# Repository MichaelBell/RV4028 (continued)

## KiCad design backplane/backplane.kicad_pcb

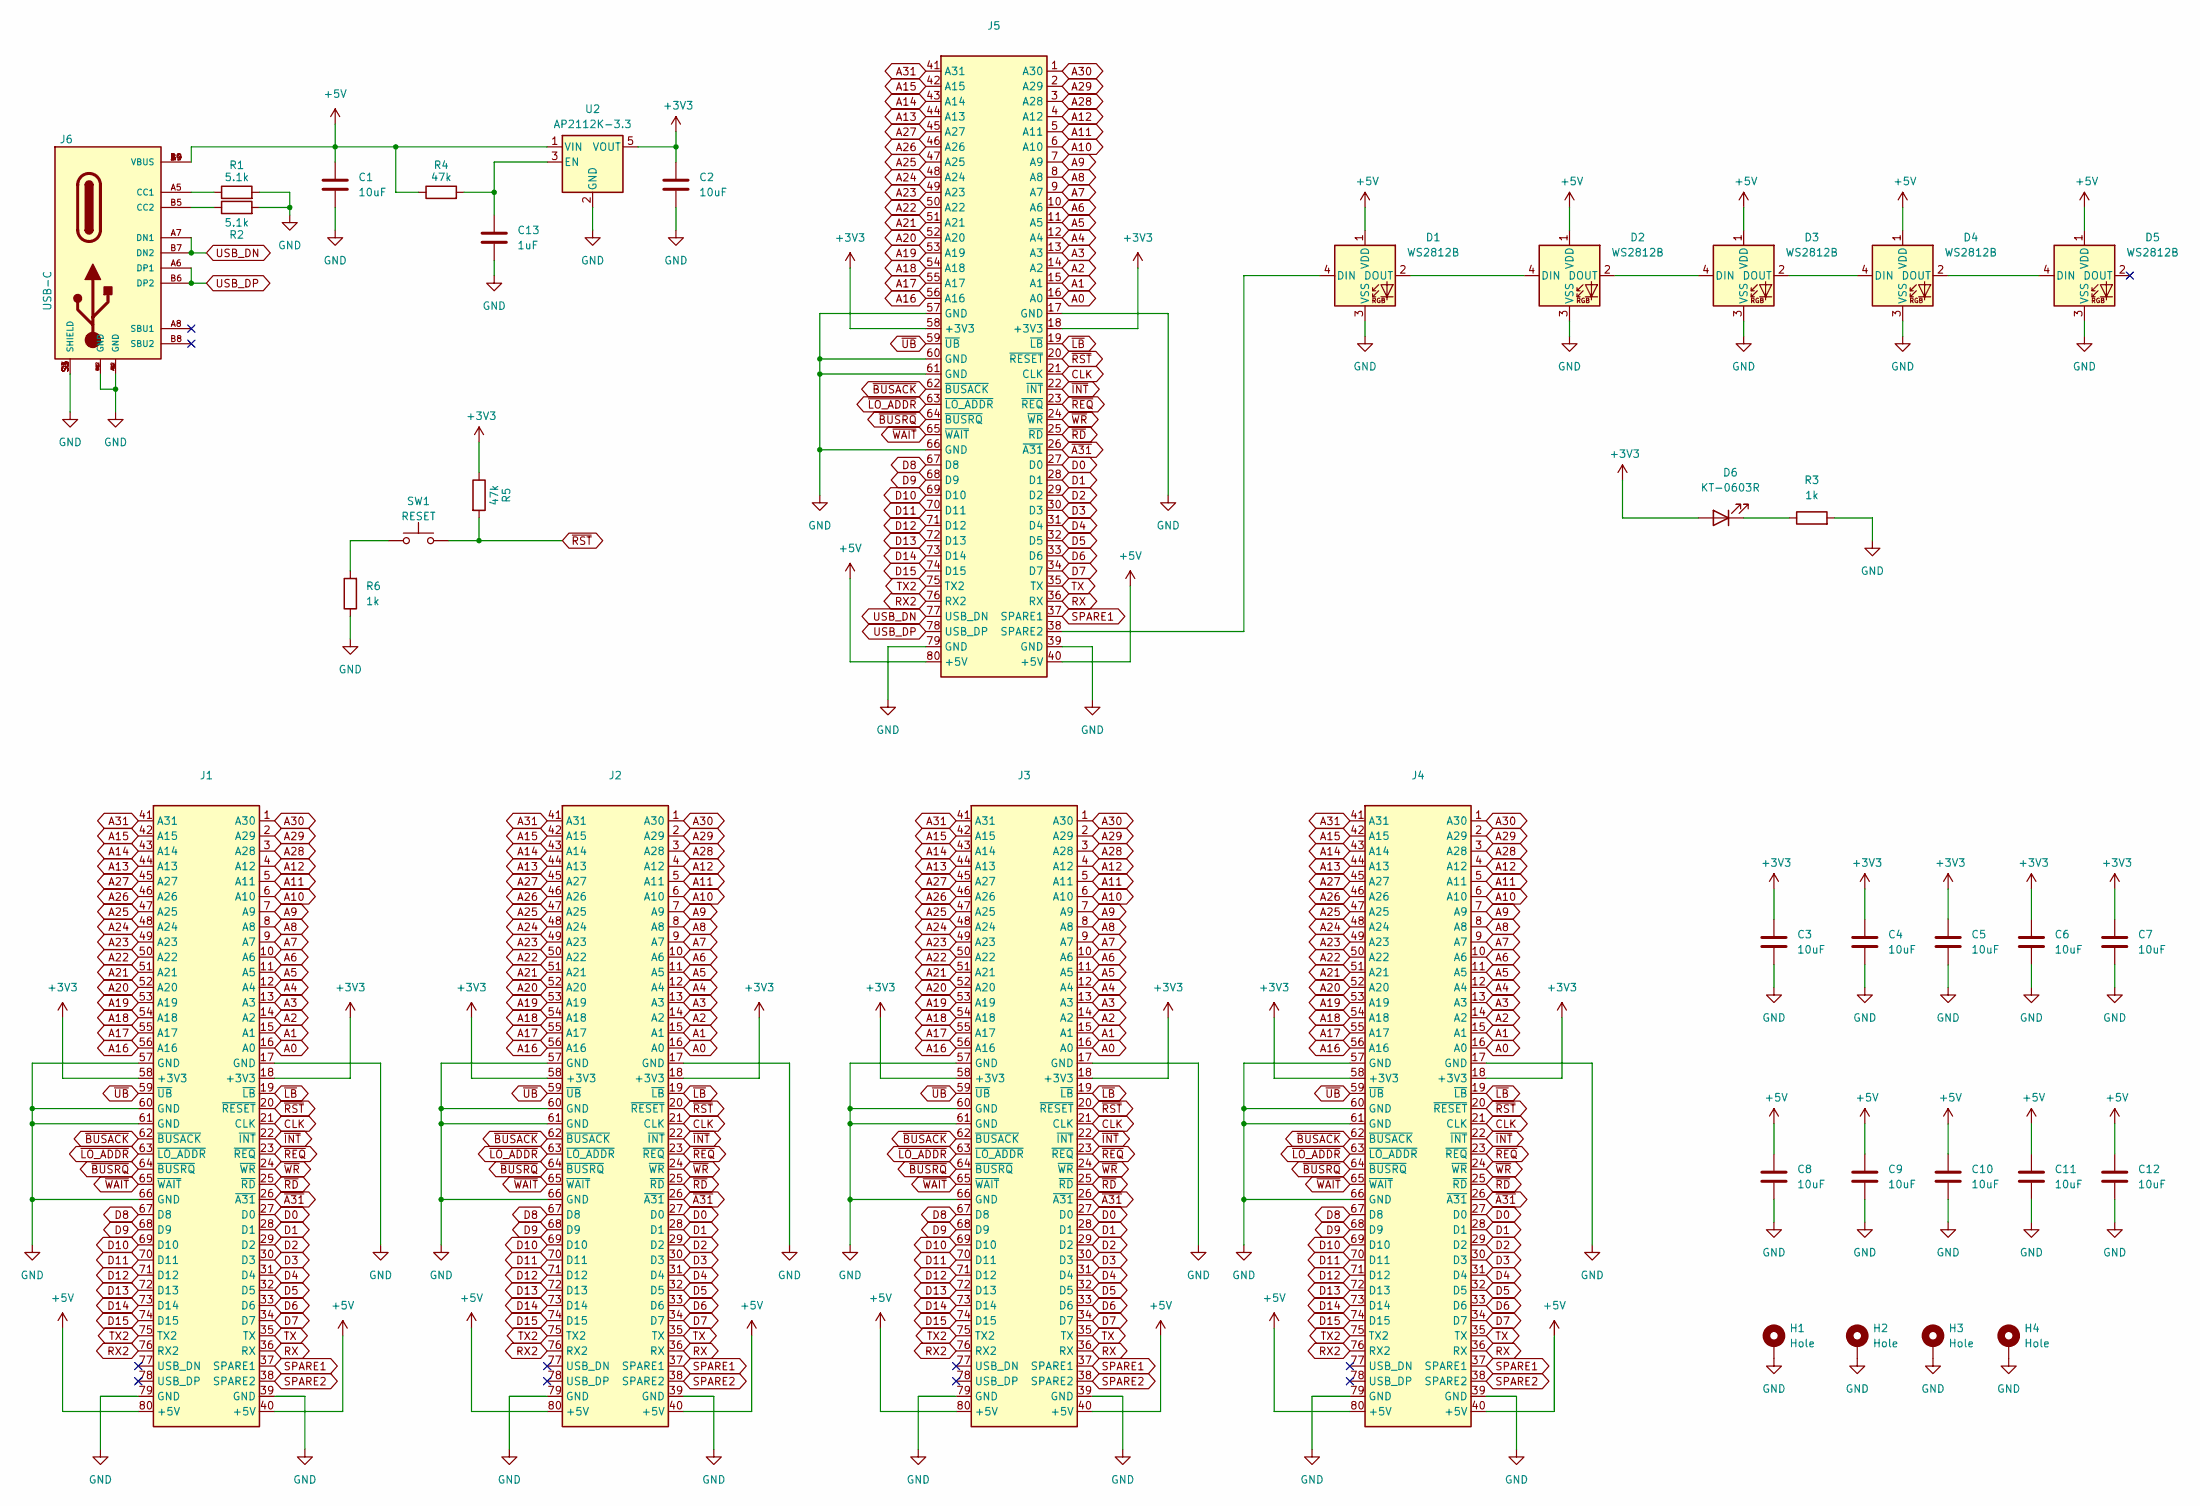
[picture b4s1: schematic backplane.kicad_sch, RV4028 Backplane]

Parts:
C1, C2, C3, C4, C5, C6, C7, C8, C9, C10, C11, C12: 10uF; C_0603_1608Metric
C13: 1uF; C_0402_1005Metric
D1, D2, D3, D4, D5: WS2812B; LED_WS2812B_PLCC4_5.0x5.0mm_P3.2mm; JLC C42417498
D6: KT-0603R; LED_0603_1608Metric; JLC C2286
H1, H2, H3, H4: Hole; MountingHole_2.7mm_M2.5_DIN965_Pad
J1, J2, J3, J4, J5: Backplane_Header_2mm; JLC C343635
J6: USB-C; TYPE-C-SMD_MC-107DJ; MPN USB4500-03-0-A; JLC C3039323
R1, R2: 5.1k; R_0402_1005Metric
R3, R6: 1k; R_0402_1005Metric
R4, R5: 47k; R_0402_1005Metric
SW1: RESET; SW-SMD_HX-TS-1101-C-W; JLC C36498960
U2: AP2112K-3.3; SOT-23-5; JLC C51118

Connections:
+3V3: C2.1, C3.1, C4.1, C5.1, C6.1, C7.1, D6.2 (A), J1.18 (+3V3), J1.58 (+3V3), J2.18 (+3V3), J2.58 (+3V3), J3.18 (+3V3), J3.58 (+3V3), J4.18 (+3V3), J4.58 (+3V3), J5.18 (+3V3), J5.58 (+3V3), R5.1, U2.5 (VOUT)
+5V: C1.1, C8.1, C9.1, C10.1, C11.1, C12.1, D1.1 (VDD), D2.1 (VDD), D3.1 (VDD), D4.1 (VDD), D5.1 (VDD), J1.40 (+5V), J1.80 (+5V), J2.40 (+5V), J2.80 (+5V), J3.40 (+5V), J3.80 (+5V), J4.40 (+5V), J4.80 (+5V), J5.40 (+5V), J5.80 (+5V), J6.A4 (VBUS), J6.A9 (VBUS), J6.B4 (VBUS), J6.B9 (VBUS), R4.1, U2.1 (VIN)
A0: J1.16 (A0), J2.16 (A0), J3.16 (A0), J4.16 (A0), J5.16 (A0)
A1: J1.15 (A1), J2.15 (A1), J3.15 (A1), J4.15 (A1), J5.15 (A1)
A2: J1.14 (A2), J2.14 (A2), J3.14 (A2), J4.14 (A2), J5.14 (A2)
A3: J1.13 (A3), J2.13 (A3), J3.13 (A3), J4.13 (A3), J5.13 (A3)
A4: J1.12 (A4), J2.12 (A4), J3.12 (A4), J4.12 (A4), J5.12 (A4)
A5: J1.11 (A5), J2.11 (A5), J3.11 (A5), J4.11 (A5), J5.11 (A5)
A6: J1.10 (A6), J2.10 (A6), J3.10 (A6), J4.10 (A6), J5.10 (A6)
A7: J1.9 (A7), J2.9 (A7), J3.9 (A7), J4.9 (A7), J5.9 (A7)
A8: J1.8 (A8), J2.8 (A8), J3.8 (A8), J4.8 (A8), J5.8 (A8)
A9: J1.7 (A9), J2.7 (A9), J3.7 (A9), J4.7 (A9), J5.7 (A9)
A10: J1.6 (A10), J2.6 (A10), J3.6 (A10), J4.6 (A10), J5.6 (A10)
A11: J1.5 (A11), J2.5 (A11), J3.5 (A11), J4.5 (A11), J5.5 (A11)
A12: J1.4 (A12), J2.4 (A12), J3.4 (A12), J4.4 (A12), J5.4 (A12)
A13: J1.44 (A13), J2.44 (A13), J3.44 (A13), J4.44 (A13), J5.44 (A13)
A14: J1.43 (A14), J2.43 (A14), J3.43 (A14), J4.43 (A14), J5.43 (A14)
A15: J1.42 (A15), J2.42 (A15), J3.42 (A15), J4.42 (A15), J5.42 (A15)
A16: J1.56 (A16), J2.56 (A16), J3.56 (A16), J4.56 (A16), J5.56 (A16)
A17: J1.55 (A17), J2.55 (A17), J3.55 (A17), J4.55 (A17), J5.55 (A17)
A18: J1.54 (A18), J2.54 (A18), J3.54 (A18), J4.54 (A18), J5.54 (A18)
A19: J1.53 (A19), J2.53 (A19), J3.53 (A19), J4.53 (A19), J5.53 (A19)
A20: J1.52 (A20), J2.52 (A20), J3.52 (A20), J4.52 (A20), J5.52 (A20)
A21: J1.51 (A21), J2.51 (A21), J3.51 (A21), J4.51 (A21), J5.51 (A21)
A22: J1.50 (A22), J2.50 (A22), J3.50 (A22), J4.50 (A22), J5.50 (A22)
A23: J1.49 (A23), J2.49 (A23), J3.49 (A23), J4.49 (A23), J5.49 (A23)
A24: J1.48 (A24), J2.48 (A24), J3.48 (A24), J4.48 (A24), J5.48 (A24)
A25: J1.47 (A25), J2.47 (A25), J3.47 (A25), J4.47 (A25), J5.47 (A25)
A26: J1.46 (A26), J2.46 (A26), J3.46 (A26), J4.46 (A26), J5.46 (A26)
A27: J1.45 (A27), J2.45 (A27), J3.45 (A27), J4.45 (A27), J5.45 (A27)
A28: J1.3 (A28), J2.3 (A28), J3.3 (A28), J4.3 (A28), J5.3 (A28)
A29: J1.2 (A29), J2.2 (A29), J3.2 (A29), J4.2 (A29), J5.2 (A29)
A30: J1.1 (A30), J2.1 (A30), J3.1 (A30), J4.1 (A30), J5.1 (A30)
A31: J1.41 (A31), J2.41 (A31), J3.41 (A31), J4.41 (A31), J5.41 (A31)
CLK: J1.21 (CLK), J2.21 (CLK), J3.21 (CLK), J4.21 (CLK), J5.21 (CLK)
D0: J1.27 (D0), J2.27 (D0), J3.27 (D0), J4.27 (D0), J5.27 (D0)
D1: J1.28 (D1), J2.28 (D1), J3.28 (D1), J4.28 (D1), J5.28 (D1)
D2: J1.29 (D2), J2.29 (D2), J3.29 (D2), J4.29 (D2), J5.29 (D2)
D3: J1.30 (D3), J2.30 (D3), J3.30 (D3), J4.30 (D3), J5.30 (D3)
D4: J1.31 (D4), J2.31 (D4), J3.31 (D4), J4.31 (D4), J5.31 (D4)
D5: J1.32 (D5), J2.32 (D5), J3.32 (D5), J4.32 (D5), J5.32 (D5)
D6: J1.33 (D6), J2.33 (D6), J3.33 (D6), J4.33 (D6), J5.33 (D6)
D7: J1.34 (D7), J2.34 (D7), J3.34 (D7), J4.34 (D7), J5.34 (D7)
D8: J1.67 (D8), J2.67 (D8), J3.67 (D8), J4.67 (D8), J5.67 (D8)
D9: J1.68 (D9), J2.68 (D9), J3.68 (D9), J4.68 (D9), J5.68 (D9)
D10: J1.69 (D10), J2.69 (D10), J3.69 (D10), J4.69 (D10), J5.69 (D10)
D11: J1.70 (D11), J2.70 (D11), J3.70 (D11), J4.70 (D11), J5.70 (D11)
D12: J1.71 (D12), J2.71 (D12), J3.71 (D12), J4.71 (D12), J5.71 (D12)
D13: J1.72 (D13), J2.72 (D13), J3.72 (D13), J4.72 (D13), J5.72 (D13)
D14: J1.73 (D14), J2.73 (D14), J3.73 (D14), J4.73 (D14), J5.73 (D14)
D15: J1.74 (D15), J2.74 (D15), J3.74 (D15), J4.74 (D15), J5.74 (D15)
GND: C1.2, C2.2, C3.2, C4.2, C5.2, C6.2, C7.2, C8.2, C9.2, C10.2, C11.2, C12.2, C13.2, D1.3 (VSS), D2.3 (VSS), D3.3 (VSS), D4.3 (VSS), D5.3 (VSS), H1.1, H2.1, H3.1, H4.1, J1.17 (GND), J1.39 (GND), J1.57 (GND), J1.60 (GND), J1.61 (GND), J1.66 (GND), J1.79 (GND), J2.17 (GND), J2.39 (GND), J2.57 (GND), J2.60 (GND), J2.61 (GND), J2.66 (GND), J2.79 (GND), J3.17 (GND), J3.39 (GND), J3.57 (GND), J3.60 (GND), J3.61 (GND), J3.66 (GND), J3.79 (GND), J4.17 (GND), J4.39 (GND), J4.57 (GND), J4.60 (GND), J4.61 (GND), J4.66 (GND), J4.79 (GND), J5.17 (GND), J5.39 (GND), J5.57 (GND), J5.60 (GND), J5.61 (GND), J5.66 (GND), J5.79 (GND), J6.1 (SHIELD), J6.A1 (GND), J6.A12 (GND), J6.B1 (GND), J6.B12 (GND), J6.S1 (SHIELD), J6.S3 (SHIELD), J6.S4 (SHIELD), R1.2, R2.2, R3.2, R6.1, U2.2 (GND)
unnamed: D1.4 (DIN), J5.38 (SPARE2)
unnamed: D1.2 (DOUT), D2.4 (DIN)
unnamed: D2.2 (DOUT), D3.4 (DIN)
unnamed: D3.2 (DOUT), D4.4 (DIN)
unnamed: D4.2 (DOUT), D5.4 (DIN)
unnamed: D6.1 (K), R3.1
unnamed: J6.A5 (CC1), R1.1
unnamed: J6.B5 (CC2), R2.1
unnamed: R6.2, SW1.1
unnamed: C13.1, R4.2, U2.3 (EN)
RX: J1.36 (RX), J2.36 (RX), J3.36 (RX), J4.36 (RX), J5.36 (RX)
RX2: J1.76 (RX2), J2.76 (RX2), J3.76 (RX2), J4.76 (RX2), J5.76 (RX2)
SPARE1: J1.37 (SPARE1), J2.37 (SPARE1), J3.37 (SPARE1), J4.37 (SPARE1), J5.37 (SPARE1)
SPARE2: J1.38 (SPARE2), J2.38 (SPARE2), J3.38 (SPARE2), J4.38 (SPARE2)
TX: J1.35 (TX), J2.35 (TX), J3.35 (TX), J4.35 (TX), J5.35 (TX)
TX2: J1.75 (TX2), J2.75 (TX2), J3.75 (TX2), J4.75 (TX2), J5.75 (TX2)
USB_DN: J5.77 (USB_DN), J6.A7 (DN1), J6.B7 (DN2)
USB_DP: J5.78 (USB_DP), J6.A6 (DP1), J6.B6 (DP2)
~A31: J1.26 (~A31), J2.26 (~A31), J3.26 (~A31), J4.26 (~A31), J5.26 (~A31)
~BUSACK: J1.62 (~BUSACK), J2.62 (~BUSACK), J3.62 (~BUSACK), J4.62 (~BUSACK), J5.62 (~BUSACK)
~BUSRQ: J1.64 (~BUSRQ), J2.64 (~BUSRQ), J3.64 (~BUSRQ), J4.64 (~BUSRQ), J5.64 (~BUSRQ)
~INT: J1.22 (~INT), J2.22 (~INT), J3.22 (~INT), J4.22 (~INT), J5.22 (~INT)
~LB: J1.19 (~LB), J2.19 (~LB), J3.19 (~LB), J4.19 (~LB), J5.19 (~LB)
~LO_ADDR: J1.63 (~LO_ADDR), J2.63 (~LO_ADDR), J3.63 (~LO_ADDR), J4.63 (~LO_ADDR), J5.63 (~LO_ADDR)
~RD: J1.25 (~RD), J2.25 (~RD), J3.25 (~RD), J4.25 (~RD), J5.25 (~RD)
~REQ: J1.23 (~REQ), J2.23 (~REQ), J3.23 (~REQ), J4.23 (~REQ), J5.23 (~REQ)
~RST: J1.20 (~RESET), J2.20 (~RESET), J3.20 (~RESET), J4.20 (~RESET), J5.20 (~RESET), R5.2, SW1.2
~UB: J1.59 (~UB), J2.59 (~UB), J3.59 (~UB), J4.59 (~UB), J5.59 (~UB)
~WAIT: J1.65 (~WAIT), J2.65 (~WAIT), J3.65 (~WAIT), J4.65 (~WAIT), J5.65 (~WAIT)
~WR: J1.24 (~WR), J2.24 (~WR), J3.24 (~WR), J4.24 (~WR), J5.24 (~WR)

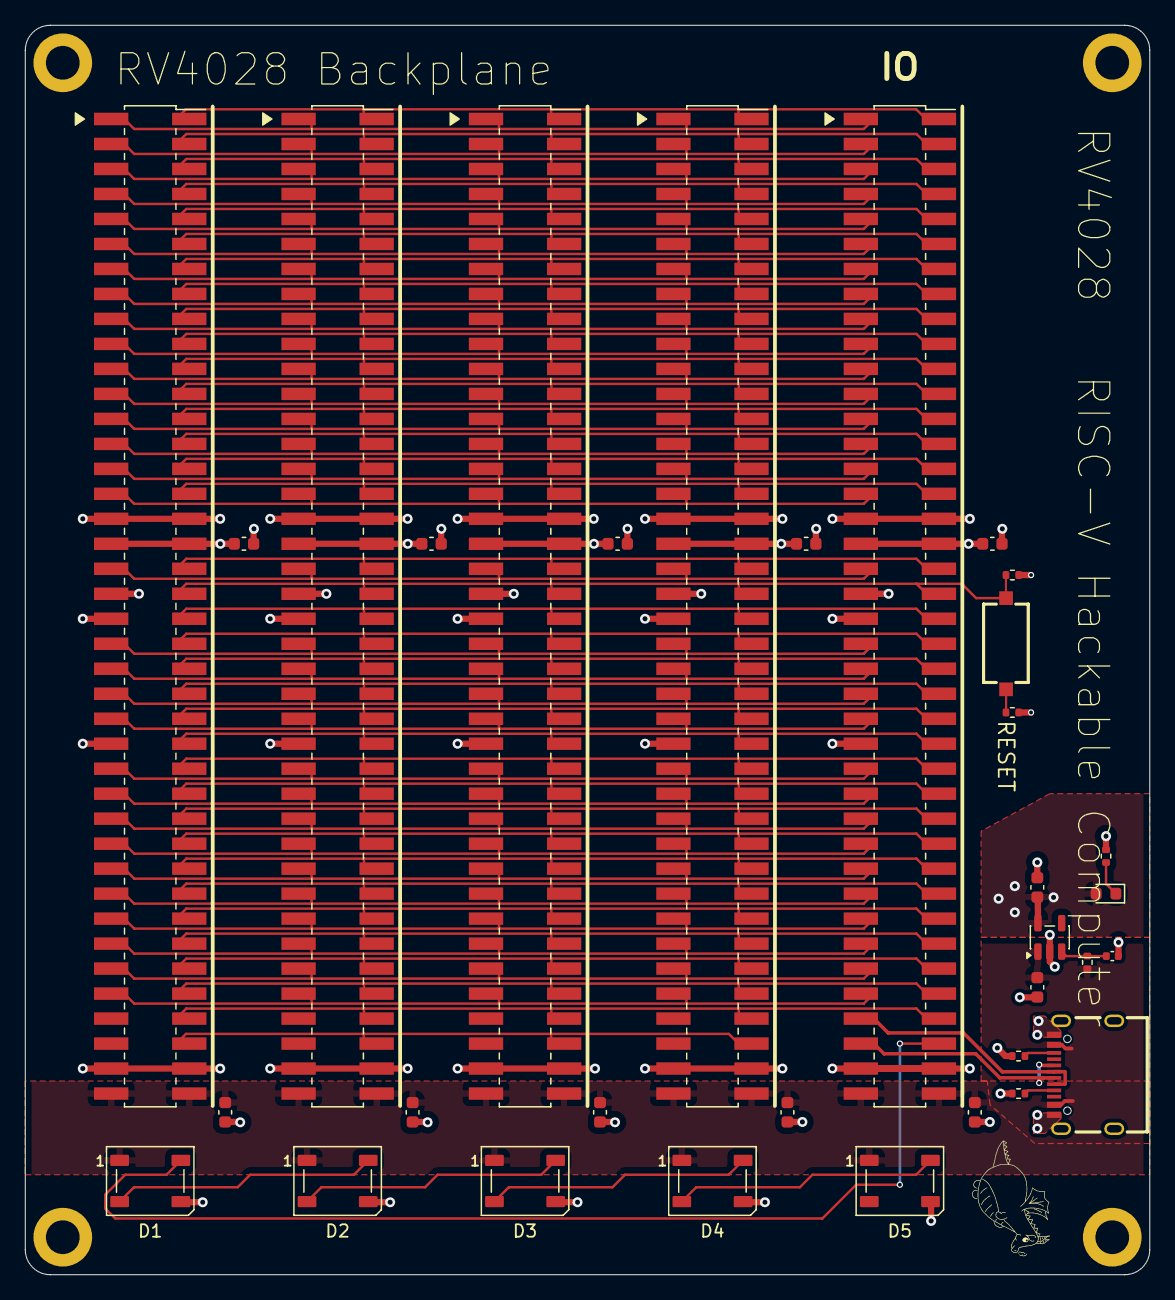
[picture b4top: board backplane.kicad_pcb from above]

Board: 4 copper layers, 90.0 x 100.0 mm, 37 parts (0 on the bottom side), 82 nets.

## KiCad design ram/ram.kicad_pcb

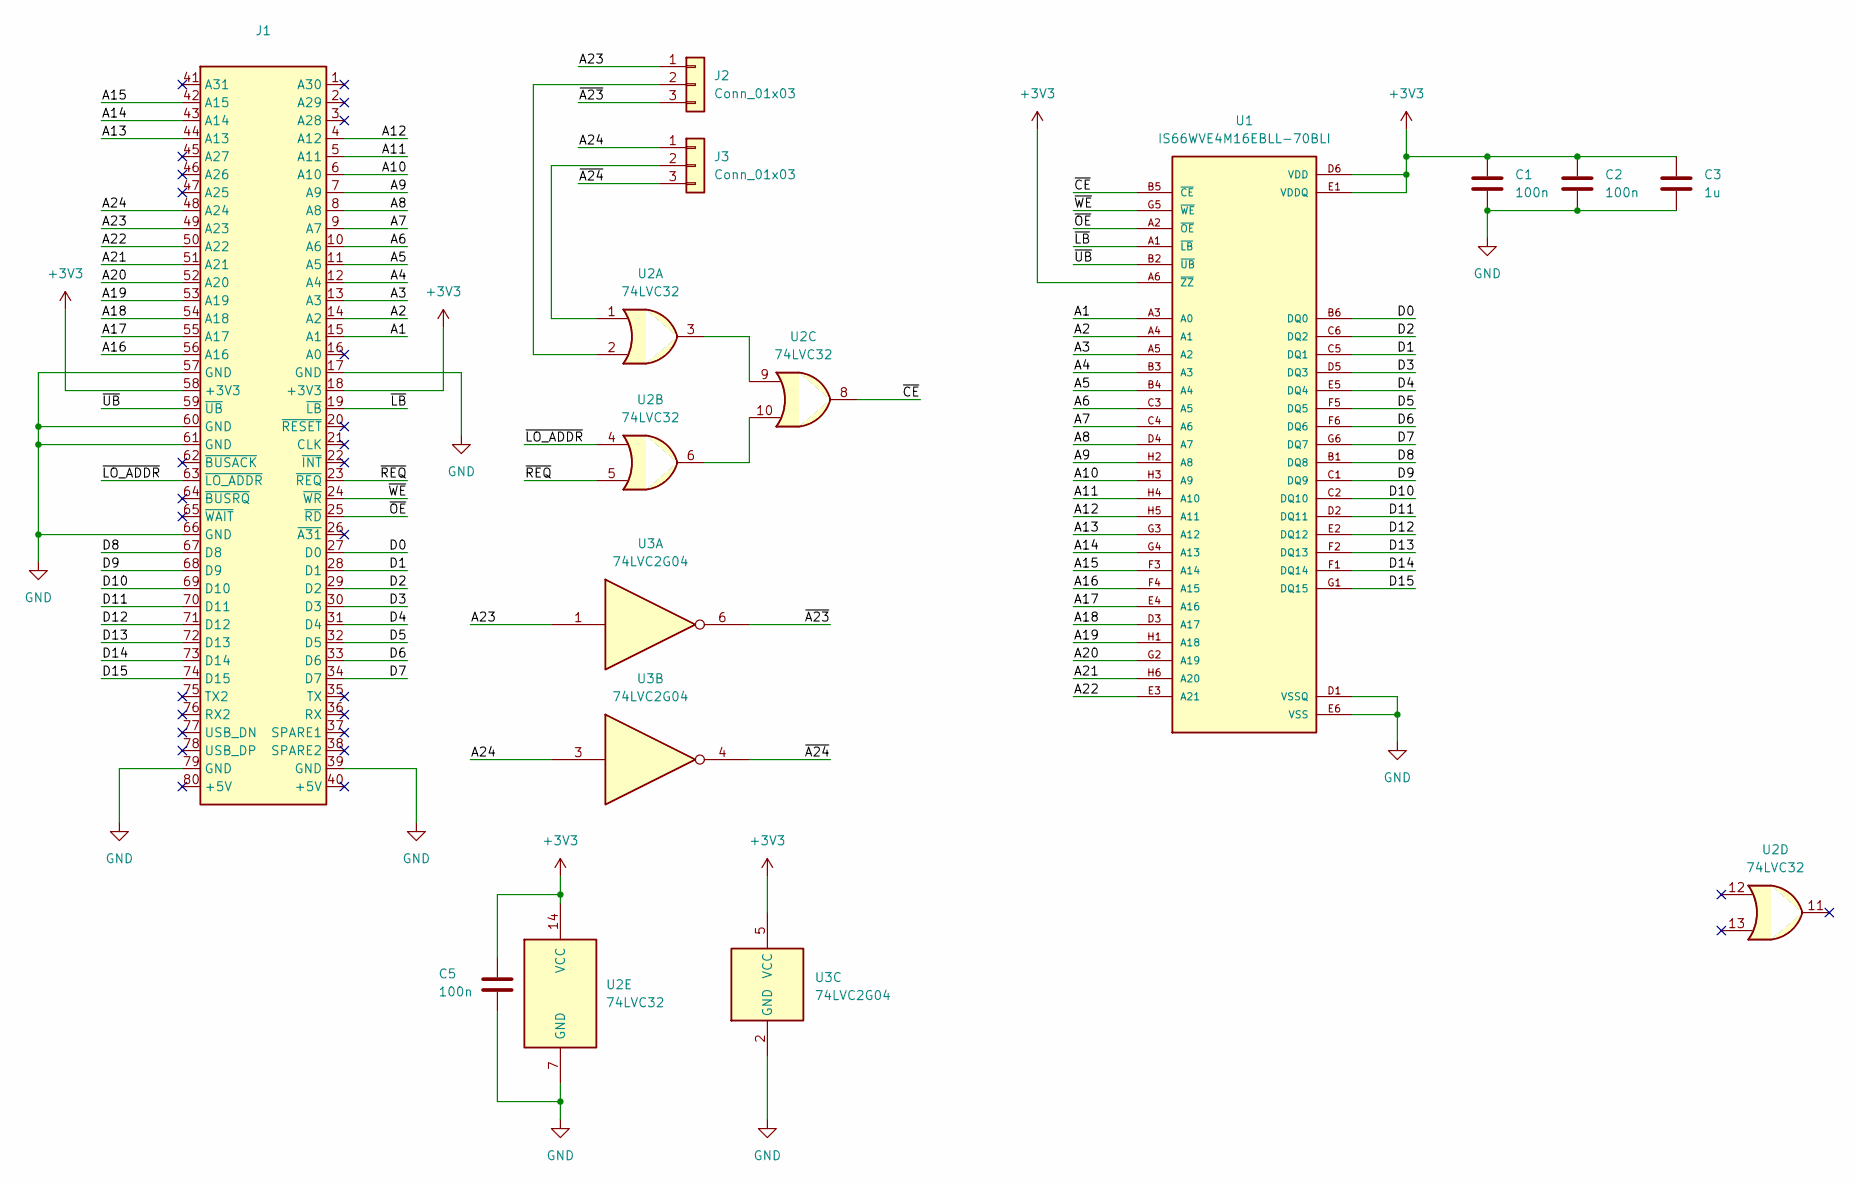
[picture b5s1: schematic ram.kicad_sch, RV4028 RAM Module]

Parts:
C1, C2, C5: 100n; C_0402_1005Metric
C3: 1u; C_0603_1608Metric
J1: Module_2mm; JLC C3407
J2, J3: Conn_01x03; PinHeader_1x03_P2.54mm_Vertical; JLC C49257
U1: IS66WVE4M16EBLL-70BLI; BGA48C75P8X6_800X600X120N; PARTREV D2; JLC C1350157
U2: 74LVC32; SSOP-14_5.3x6.2mm_P0.65mm; JLC C2867091
U3: 74LVC2G04; SOT-363_SC-70-6; JLC C105251

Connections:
+3V3: C1.1, C2.1, C3.1, C5.1, J1.18 (+3V3), J1.58 (+3V3), U1.A6 (~ZZ), U1.D6 (VDD), U1.E1 (VDDQ), U2.14 (VCC), U3.5 (VCC)
/A1: J1.15 (A1), U1.A3 (A0)
/A2: J1.14 (A2), U1.A4 (A1)
/A3: J1.13 (A3), U1.A5 (A2)
/A4: J1.12 (A4), U1.B3 (A3)
/A5: J1.11 (A5), U1.B4 (A4)
/A6: J1.10 (A6), U1.C3 (A5)
/A7: J1.9 (A7), U1.C4 (A6)
/A8: J1.8 (A8), U1.D4 (A7)
/A9: J1.7 (A9), U1.H2 (A8)
/A10: J1.6 (A10), U1.H3 (A9)
/A11: J1.5 (A11), U1.H4 (A10)
/A12: J1.4 (A12), U1.H5 (A11)
/A13: J1.44 (A13), U1.G3 (A12)
/A14: J1.43 (A14), U1.G4 (A13)
/A15: J1.42 (A15), U1.F3 (A14)
/A16: J1.56 (A16), U1.F4 (A15)
/A17: J1.55 (A17), U1.E4 (A16)
/A18: J1.54 (A18), U1.D3 (A17)
/A19: J1.53 (A19), U1.H1 (A18)
/A20: J1.52 (A20), U1.G2 (A19)
/A21: J1.51 (A21), U1.H6 (A20)
/A22: J1.50 (A22), U1.E3 (A21)
/A23: J1.49 (A23), J2.1, U3.1
/A24: J1.48 (A24), J3.1, U3.3
/D0: J1.27 (D0), U1.B6 (DQ0)
/D1: J1.28 (D1), U1.C5 (DQ1)
/D2: J1.29 (D2), U1.C6 (DQ2)
/D3: J1.30 (D3), U1.D5 (DQ3)
/D4: J1.31 (D4), U1.E5 (DQ4)
/D5: J1.32 (D5), U1.F5 (DQ5)
/D6: J1.33 (D6), U1.F6 (DQ6)
/D7: J1.34 (D7), U1.G6 (DQ7)
/D8: J1.67 (D8), U1.B1 (DQ8)
/D9: J1.68 (D9), U1.C1 (DQ9)
/D10: J1.69 (D10), U1.C2 (DQ10)
/D11: J1.70 (D11), U1.D2 (DQ11)
/D12: J1.71 (D12), U1.E2 (DQ12)
/D13: J1.72 (D13), U1.F2 (DQ13)
/D14: J1.73 (D14), U1.F1 (DQ14)
/D15: J1.74 (D15), U1.G1 (DQ15)
/~A23: J2.3, U3.6
/~A24: J3.3, U3.4
/~CE: U1.B5 (~CE), U2.8
/~LB: J1.19 (~LB), U1.A1 (~LB)
/~LO_ADDR: J1.63 (~LO_ADDR), U2.4
/~OE: J1.25 (~RD), U1.A2 (~OE)
/~REQ: J1.23 (~REQ), U2.5
/~UB: J1.59 (~UB), U1.B2 (~UB)
/~WE: J1.24 (~WR), U1.G5 (~WE)
GND: C1.2, C2.2, C3.2, C5.2, J1.17 (GND), J1.39 (GND), J1.57 (GND), J1.60 (GND), J1.61 (GND), J1.66 (GND), J1.79 (GND), U1.D1 (VSSQ), U1.E6 (VSS), U2.7 (GND), U3.2 (GND)
unnamed: J2.2, U2.2
unnamed: J3.2, U2.1
unnamed: U2.3, U2.9
unnamed: U2.6, U2.10

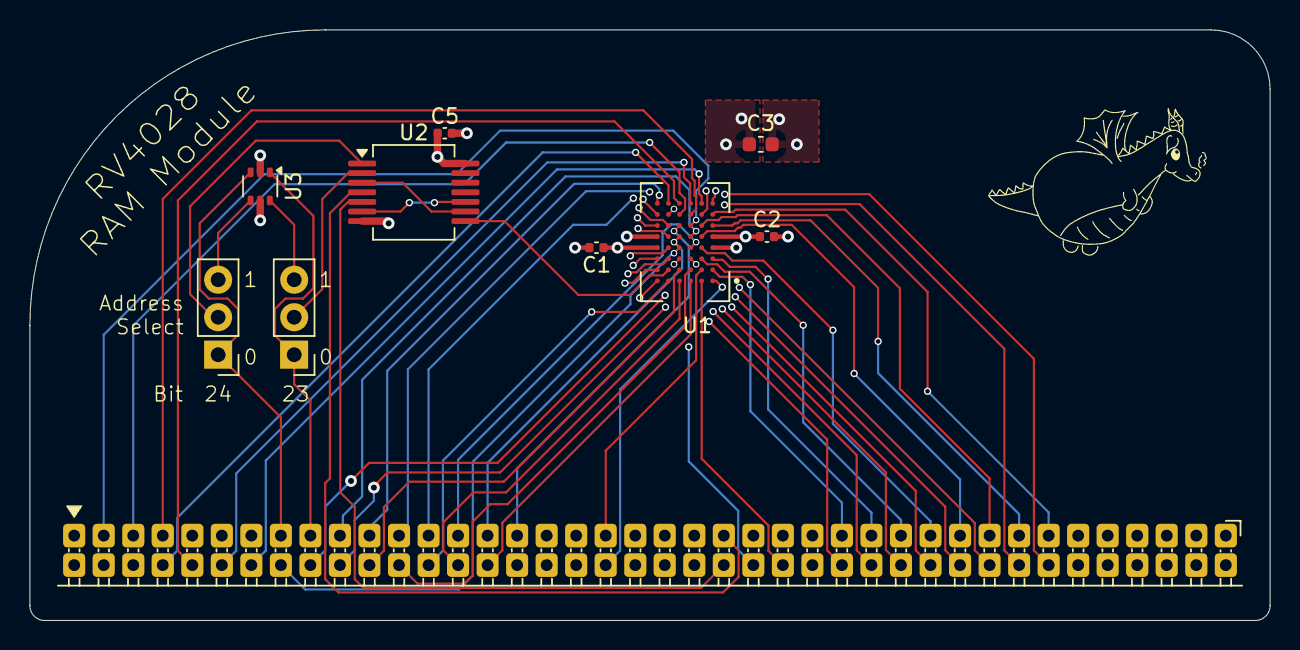
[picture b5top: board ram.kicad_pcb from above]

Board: 4 copper layers, 84.0 x 40.0 mm, 10 parts (0 on the bottom side), 55 nets.

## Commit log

2025-10-24 Bus image
2025-10-25 Work out memory cycles, more documentation
2025-10-25 Update pin names
2025-10-25 Rearrange pins to improve routability
2025-10-25 Update images
2025-10-27 CPU module
2025-10-27 Updates to match CPU module design
2025-10-31 Improve power. Start work on IO module
2025-12-25 Add 4kB ROM to gateware
2025-12-25 Updates to io board
2025-12-26 Fix module pin labels
2026-01-02 IO module routed
2026-01-12 RAM module, many tweaks
2026-01-13 BGA layout is a pain
2026-01-13 Revised module header
2026-01-14 Relayout CPU
2026-01-19 IO module 2mm headers
2026-01-19 CPU and IO production fixes
2026-01-21 Add backplane
2026-01-21 Update gitignore
2026-01-22 RAM board attempt 2
2026-01-22 PDFs of schematics, readme updates
2026-01-22 Backplane reset and fixes
2026-01-22 Finish RAM module routing
2026-01-22 Tweaks
2026-01-23 Pull up on REQ
2026-01-25 Mounting holes
2026-01-28 Review before first PCB order
2026-01-29 Implement interrupts
2026-01-29 Smaller ALU
2026-01-29 Larger ROM
2026-01-29 Interrupts work, but too big
2026-01-29 Possible option
2026-01-30 Make it fit
2026-01-31 Updates from ICE40 checklist
2026-02-01 Test and fix short accesses, reset sync
2026-02-16 Get CPU working
2026-02-18 Fix WAIT
2026-02-18 CPU bootloader
2026-02-20 Multiple SB test
2026-02-22 Bootloader clears LEDs
